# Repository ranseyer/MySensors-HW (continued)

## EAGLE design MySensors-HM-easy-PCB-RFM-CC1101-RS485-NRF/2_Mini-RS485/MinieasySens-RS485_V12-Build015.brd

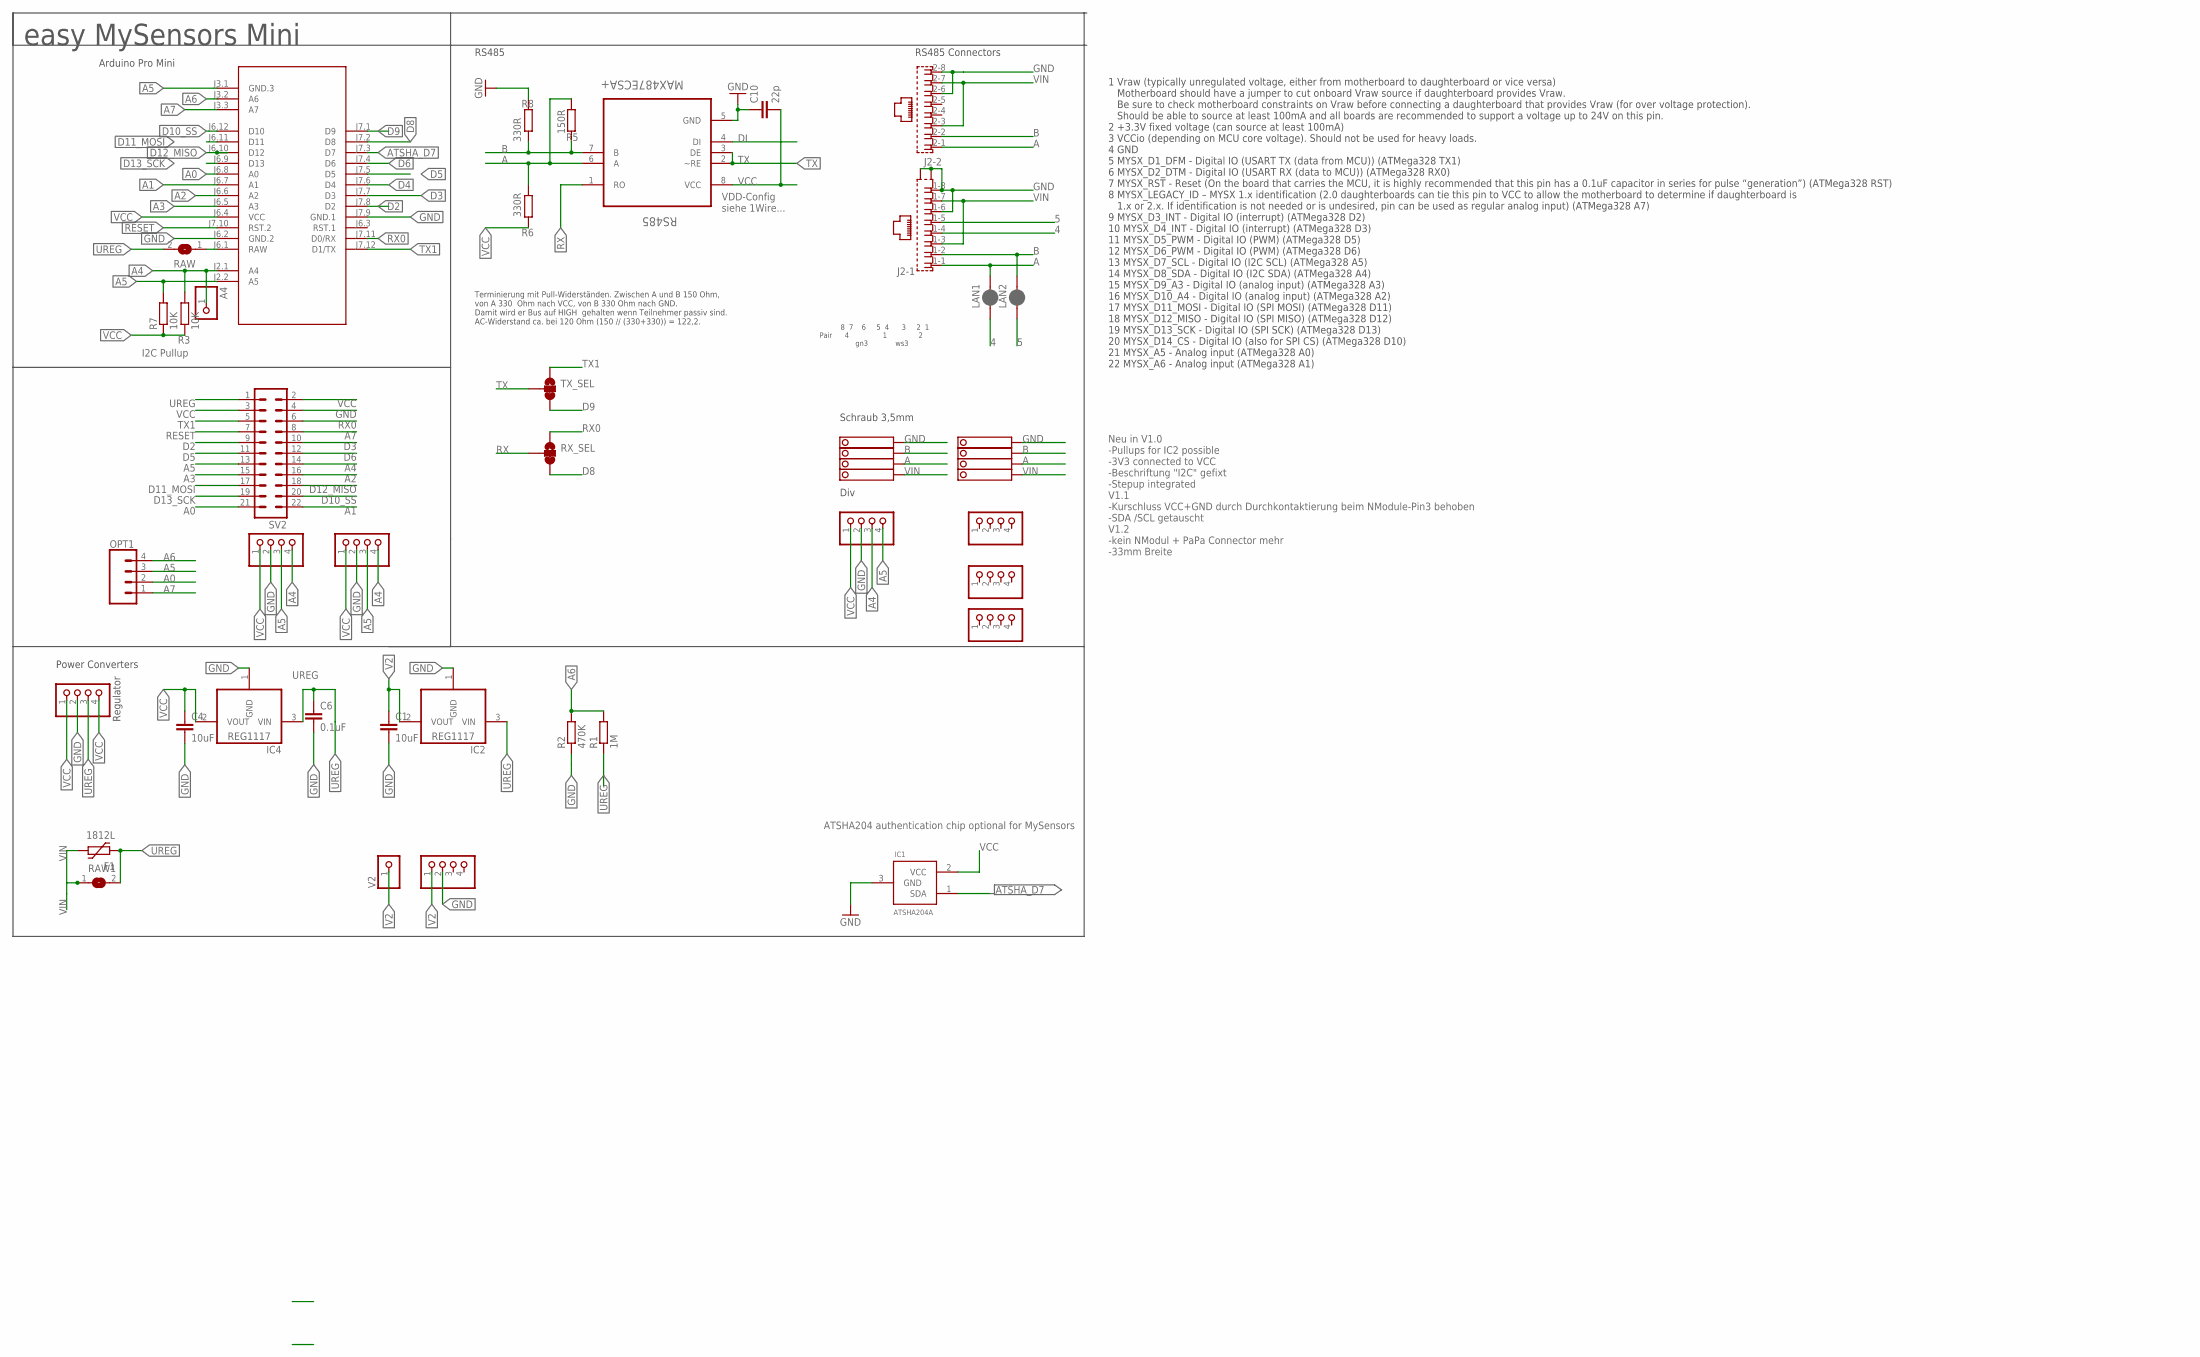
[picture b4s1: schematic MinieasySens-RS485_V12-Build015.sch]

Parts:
A4: PINHD-1X1; 1X01
BH1750: PINHD-1X04_2.54-S; 1X04-S
C1, C4: 10uF; C1210
C6: 0.1uF; C1206
C10: 22p; C0805
F1: 1812L
I2C-1, I2C-2: PINHD-1X04_2.54-S; 1X04-S
IC1: ATSHA204A; SOT23
IC2, IC4: REG1117; SOT223
J2: RJ45_2X_NARROW_SHILDPINS_NOCASE
JP1, JP2, JP4: PINHD-1X04_2.54-S; 1X04-S
LAN1, LAN2: JUMPER-SMT_2_NC_PASTE_SILK; SMT-JUMPER_2_NC_PASTE_SILK
M1: ARDUINO-PRO-MINI-3.3V#NP; ARDUINO-PRO-MINI#NP
OPT1: CONN_04; 1X04
R1: 1M; R0805
R2: 470K; R0805
R3, R7: 10K; R0805
R5: 150R; R0805
R6, R8: 330R; R0805
RAW, RAW1: SJ
RS485: MAX487ECSA+; SOIC127P600X175-8N
RX_SEL: JUMPER-SMT_3_1-NC_TRACE_SILK; SMT-JUMPER_3_1-NC_TRACE_SILK
STEPDWN: PINHD-1X04_2.54-S; 1X04-S
SV2: MA11-2
TX_SEL: JUMPER-SMT_3_1-NC_TRACE_SILK; SMT-JUMPER_3_1-NC_TRACE_SILK
V2: PINHD-1X1; 1X01
V2-: PINHD-1X04_2.54-S; 1X04-S
X1, X4: 1751264

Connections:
4: J2.1-4 (4), LAN1.1
5: J2.1-5 (5), LAN2.1
A: J2.1-1 (1), J2.2-1 (1), LAN1.2, R5.1, R6.2, RS485.6 (A), X1.2, X4.2
A0: M1.J6.8 (A0), OPT1.2, SV2.21
A1: M1.J6.7 (A1), SV2.22
A2: M1.J6.6 (A2), SV2.16
A3: M1.J6.5 (A3), SV2.15
A4: A4.1, BH1750.4, I2C-1.4, I2C-2.3, M1.J2.1 (A4), R3.2, SV2.14
A5: BH1750.3, I2C-1.3, I2C-2.4, M1.J2.2 (A5), M1.J3.1 (GND.3), OPT1.3, R7.2, SV2.13
A6: M1.J3.2 (A6), OPT1.4, R1.2, R2.2
A7: M1.J3.3 (A7), OPT1.1, SV2.8
ATSHA_D7: IC1.1 (SDA), M1.J7.3 (D7)
B: J2.1-2 (2), J2.2-2 (2), LAN2.2, R5.2, R8.1, RS485.7 (B), X1.3, X4.3
D2: M1.J7.8 (D2), SV2.9
D3: M1.J7.7 (D3), SV2.10
D4: M1.J7.6 (D4)
D5: M1.J7.5 (D5), SV2.11
D6: M1.J7.4 (D6), SV2.12
D8: M1.J7.2 (D8), RX_SEL.3
D9: M1.J7.1 (D9), TX_SEL.3
D10_SS: M1.J6.12 (D10), SV2.20
D11_MOSI: M1.J6.11 (D11), SV2.17
D12_MISO: M1.J6.10 (D12), SV2.18
D13_SCK: M1.J6.9 (D13), SV2.19
DI: RS485.4 (DI)
GND: BH1750.2, C1.2, C4.2, C6.2, C10.1, I2C-1.2, I2C-2.2, IC1.3 (GND), IC2.1 (GND), IC4.1 (GND), J2.1-6 (6), J2.1-8 (8), J2.2-6 (6), J2.2-8 (8), J2.G1 (S1), J2.G3 (S2), M1.J6.2 (GND.2), M1.J7.9 (GND.1), R2.1, R8.2, RS485.5 (GND), STEPDWN.2, SV2.4, V2-.2, X1.4, X4.4
RAW: M1.J6.1 (RAW), RAW.1
RESET: M1.J7.10 (RST.2), SV2.7
RX: RS485.1 (RO), RX_SEL.2
RX0: M1.J7.11 (D0/RX), RX_SEL.1, SV2.6
TX: RS485.2 (~RE), RS485.3 (DE), TX_SEL.2
TX1: M1.J7.12 (D1/TX), SV2.5, TX_SEL.1
UREG: C6.1, F1.P$1 (1), IC2.3 (VIN), IC4.3 (VIN), R1.1, RAW.2, RAW1.2, STEPDWN.3, SV2.1
V2: C1.1, IC2.2 (VOUT), V2.1, V2-.1
VCC: BH1750.1, C4.1, C10.2, I2C-1.1, I2C-2.1, IC1.2 (VCC), IC4.2 (VOUT), M1.J6.4 (VCC), R3.1, R6.1, R7.1, RS485.8 (VCC), STEPDWN.1, STEPDWN.4, SV2.2, SV2.3
VIN: F1.P$2 (2), J2.1-3 (3), J2.1-7 (7), J2.2-3 (3), J2.2-7 (7), RAW1.1, X1.1, X4.1

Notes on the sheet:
easy MySensors Mini
Arduino Pro Mini
ATSHA204 authentication chip optional for MySensors
Div
Neu in V1.0 -Pullups for IC2 possible -3V3 connected to VCC -Beschriftung "I2C" gefixt -Stepup integrated V1.1 -Kurschluss VCC+GND durch Durchkontaktierung beim NModule-Pin3 behoben -SDA /SCL getauscht V1.2 -kein NModul + PaPa Connector mehr -33mm Breite
I2C Pullup
Power Converters
RS485
VDD-Config siehe 1Wire...
Terminierung mit Pull-Widerständen. Zwischen A und B 150 Ohm, von A 330 Ohm nach VCC, von B 330 Ohm nach GND. Damit wird er Bus auf HIGH gehalten wenn Teilnehmer passiv sind. AC-Widerstand ca. bei 120 Ohm (150 // (330+330)) = 122,2.
Schraub 3,5mm
8 7 6 5 4 3 2 1 Pair 4 1 2 gn3 ws3
Regulator
RS485 Connectors
1 Vraw (typically unregulated voltage, either from motherboard to daughterboard or vice versa) Motherboard should have a jumper to cut onboard Vraw source if daughterboard provides Vraw. Be sure to check motherboard constraints on Vraw before connecting a daughterboard that provides Vraw (for over 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

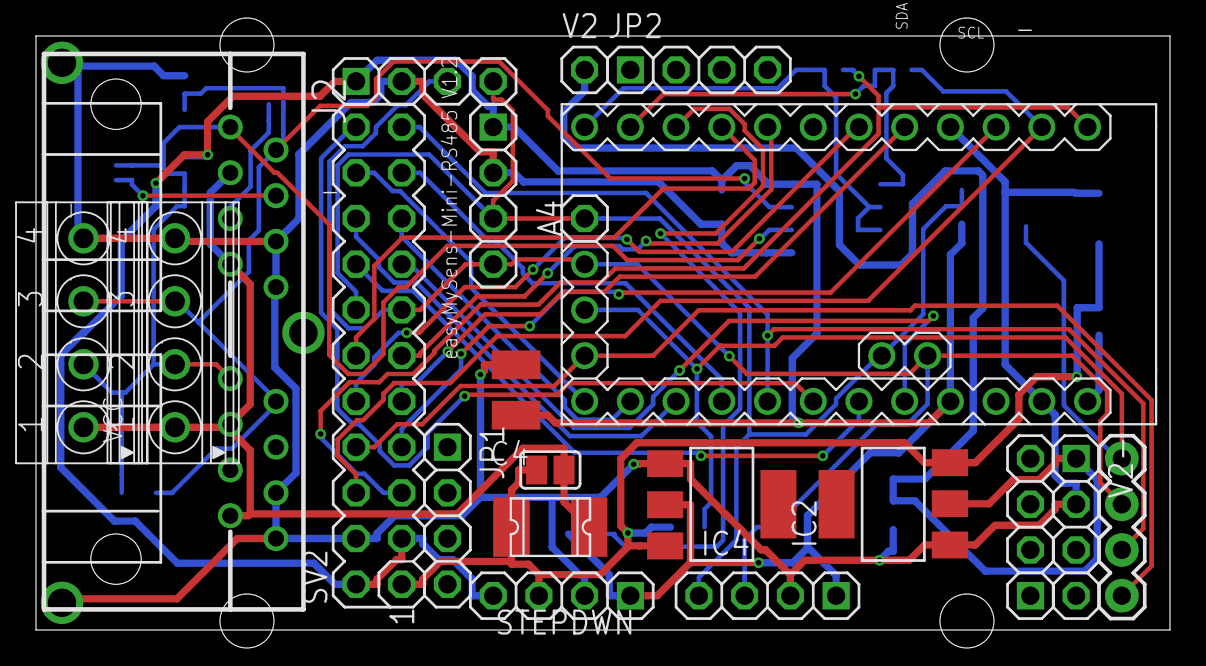
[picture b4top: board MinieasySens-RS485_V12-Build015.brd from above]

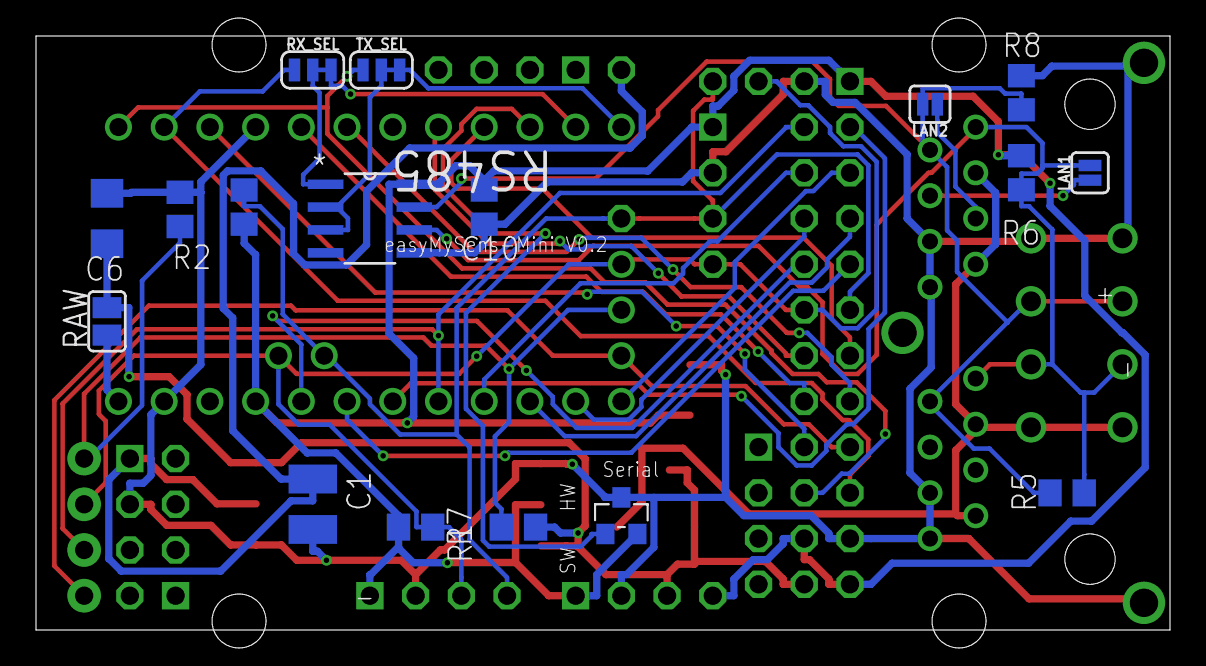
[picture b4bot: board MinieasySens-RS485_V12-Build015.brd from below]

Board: 2 copper layers, 63.0 x 33.0 mm, 38 parts (17 on the bottom side), 34 nets.

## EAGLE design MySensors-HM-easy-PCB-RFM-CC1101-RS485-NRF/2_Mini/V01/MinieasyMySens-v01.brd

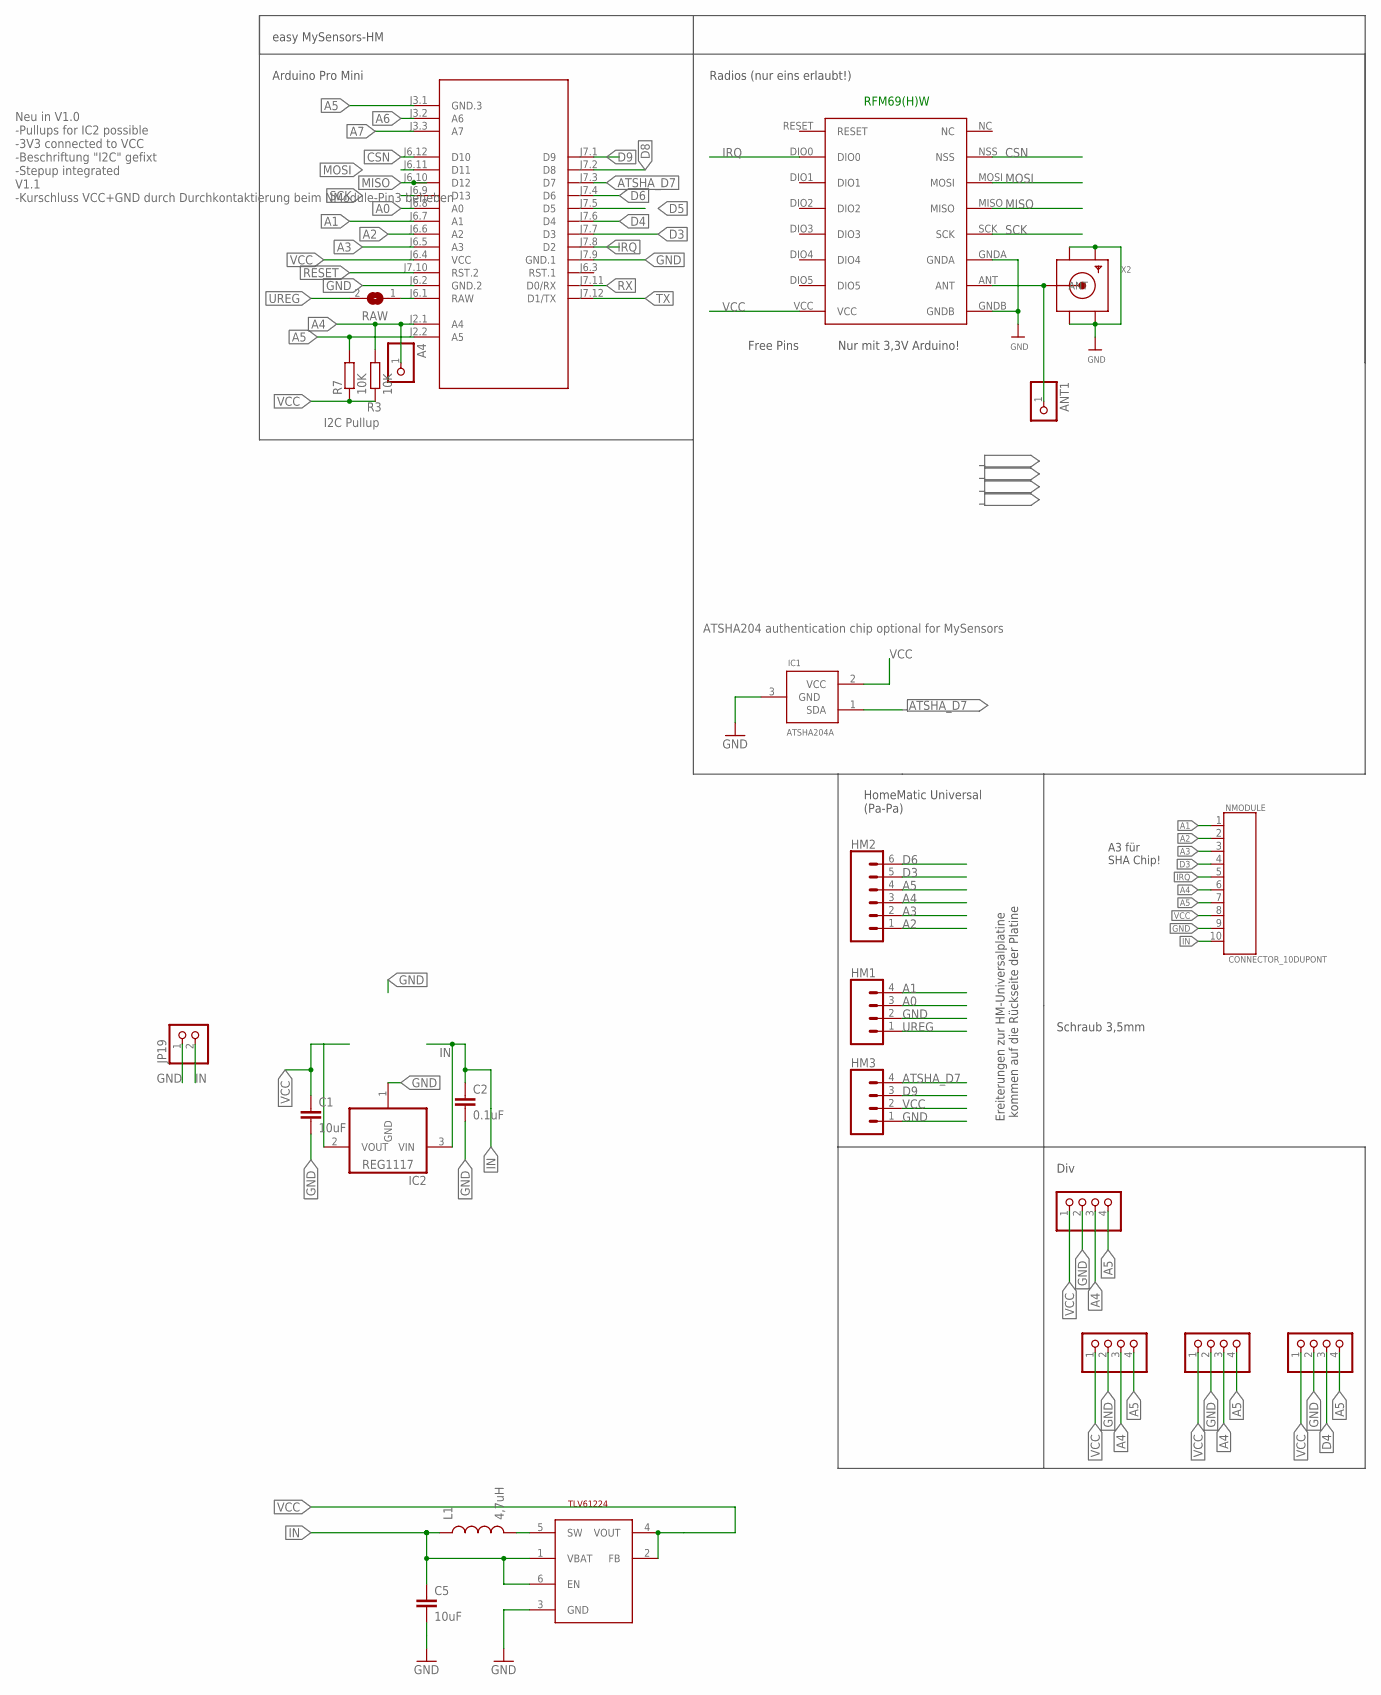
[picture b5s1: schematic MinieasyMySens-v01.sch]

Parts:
A4: PINHD-1X1; 1X01
ANT1: PINHD-1X1; 1X01
BH1750: PINHD-1X04_2.54-S; 1X04-S
C1: 10uF; C1210
C2: 0.1uF; C1206
C5: 10uF; 0805
HM1, HM3: CONN_04; 1X04
HM2: CONN_06SILK_FEMALE_PTH; 1X06
I2C-1, I2C-2: PINHD-1X04_2.54-S; 1X04-S
IC1: ATSHA204A; SOT23
IC2: REG1117; SOT223
JP19: PINHD-1X2; 1X02
L1: 4,7uH; 0805
M1: ARDUINO-PRO-MINI-3.3V#NP; ARDUINO-PRO-MINI#NP
MOTION: PINHD-1X04_2.54-S; 1X04-S
NMODULE: CONNECTOR_10DUPONT; DUPONT_10
R3, R7: 10K; R0805
RAW: SJ
RFM69W: RFM69HW; RFM
STEPUP: TLV61224; SOT23-6L
X2: SMACONNECTOR_EDGE; SMA_EDGELAUNCH

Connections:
A0: HM1.3, M1.J6.8 (A0)
A1: HM1.4, M1.J6.7 (A1), NMODULE.1
A2: HM2.1, M1.J6.6 (A2), NMODULE.2
A3: HM2.2, M1.J6.5 (A3), NMODULE.3
A4: A4.1, BH1750.3, HM2.3, I2C-1.3, I2C-2.3, M1.J2.1 (A4), NMODULE.6, R3.2
A5: BH1750.4, HM2.4, I2C-1.4, I2C-2.4, M1.J2.2 (A5), M1.J3.1 (GND.3), MOTION.4, NMODULE.7, R7.2
A6: M1.J3.2 (A6)
A7: M1.J3.3 (A7)
ATSHA_D7: HM3.4, IC1.1 (SDA), M1.J7.3 (D7)
CSN: M1.J6.12 (D10), RFM69W.NSS
D3: HM2.5, M1.J7.7 (D3), NMODULE.4
D4: M1.J7.6 (D4), MOTION.3
D5: M1.J7.5 (D5)
D6: HM2.6, M1.J7.4 (D6)
D8: M1.J7.2 (D8)
D9: HM3.3, M1.J7.1 (D9)
GND: BH1750.2, C1.2, C2.2, C5.2, HM1.2, HM3.1, I2C-1.2, I2C-2.2, IC1.3 (GND), IC2.1 (GND), JP19.1, M1.J6.2 (GND.2), M1.J7.9 (GND.1), MOTION.2, NMODULE.9, RFM69W.GNDA, RFM69W.GNDB, STEPUP.3 (GND), X2.GND@1 (GND4), X2.GND@2 (GND3), X2.GND@3 (GND2), X2.GND@4 (GND1)
IN: C2.1, C5.1, IC2.3 (VIN), JP19.2, L1.1, NMODULE.10, STEPUP.1 (VBAT), STEPUP.6 (EN)
IRQ: M1.J7.8 (D2), NMODULE.5, RFM69W.DIO0
MISO: M1.J6.10 (D12), RFM69W.MISO
MOSI: M1.J6.11 (D11), RFM69W.MOSI
unnamed: L1.2, STEPUP.5 (SW)
unnamed: ANT1.1, RFM69W.ANT, X2.P (ANT)
RAW: M1.J6.1 (RAW), RAW.1
RESET: M1.J7.10 (RST.2)
RX: M1.J7.11 (D0/RX)
SCK: M1.J6.9 (D13), RFM69W.SCK
TX: M1.J7.12 (D1/TX)
UREG: HM1.1, RAW.2
VCC: BH1750.1, C1.1, HM3.2, I2C-1.1, I2C-2.1, IC1.2 (VCC), IC2.2 (VOUT), M1.J6.4 (VCC), MOTION.1, NMODULE.8, R3.1, R7.1, RFM69W.VCC, STEPUP.2 (FB), STEPUP.4 (VOUT)

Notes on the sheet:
easy MySensors-HM
Arduino Pro Mini
Free Pins
ATSHA204 authentication chip optional for MySensors
RFM69(H)W
Nur mit 3,3V Arduino!
A3 für SHA Chip!
Ereiterungen zur HM-Universalplatine kommen auf die Rückseite der Platine
HomeMatic Universal (Pa-Pa)
Schraub 3,5mm
Div
Radios (nur eins erlaubt!)
Neu in V1.0 -Pullups for IC2 possible -3V3 connected to VCC -Beschriftung "I2C" gefixt -Stepup integrated V1.1 -Kurschluss VCC+GND durch Durchkontaktierung beim NModule-Pin3 beheben
I2C Pullup

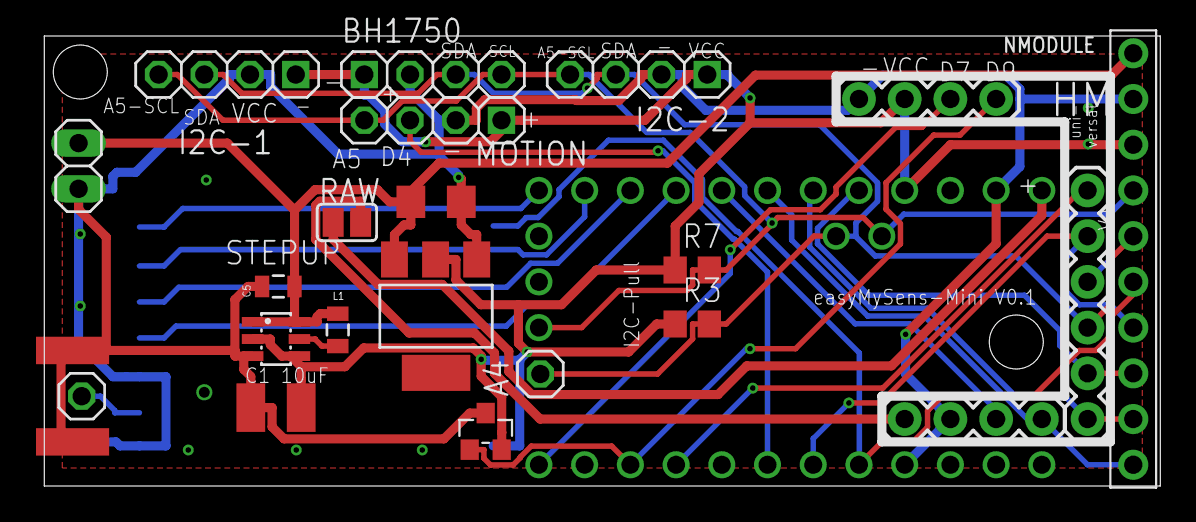
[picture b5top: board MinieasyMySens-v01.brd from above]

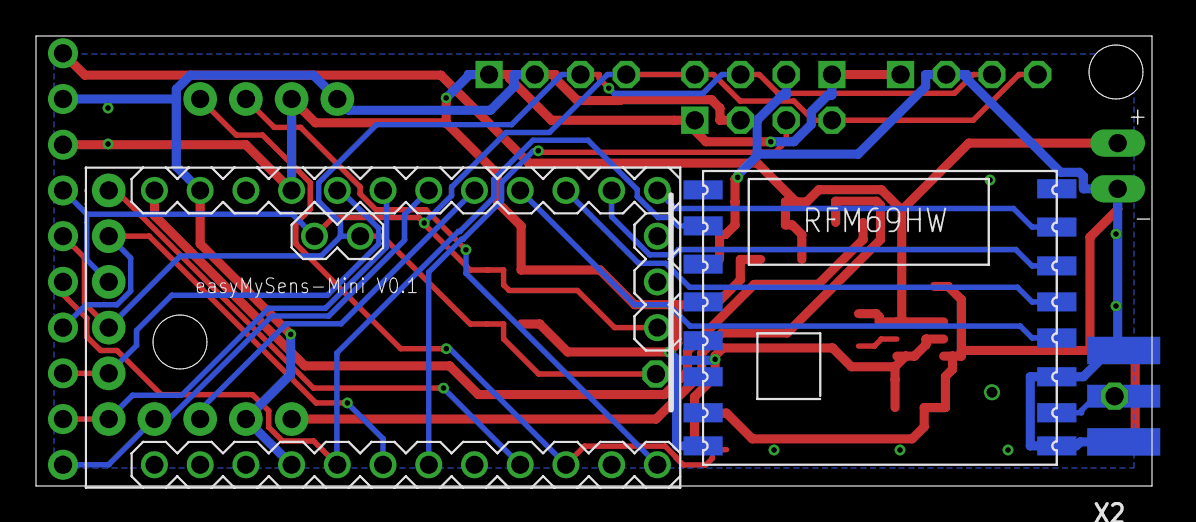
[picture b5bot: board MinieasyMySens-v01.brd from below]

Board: 2 copper layers, 62.0 x 25.0 mm, 24 parts (3 on the bottom side), 23 nets.
